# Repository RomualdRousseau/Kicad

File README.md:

# Kicad
Various Kicad Sketches to test new ideas

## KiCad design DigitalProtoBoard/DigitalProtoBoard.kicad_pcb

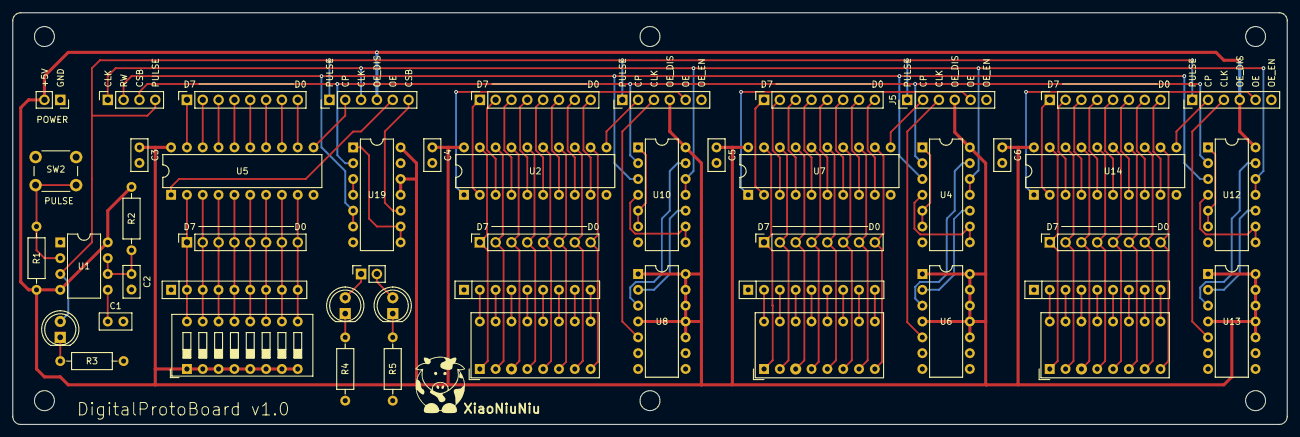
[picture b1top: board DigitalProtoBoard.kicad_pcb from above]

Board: 2 copper layers, 204.5 x 66.0 mm, 57 parts (0 on the bottom side), 128 nets.

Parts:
BAR1, BAR2, BAR3: SSB-LXH100SRW
C1, C2: 10nF; C_Disc_D5.0mm_W2.5mm_P2.50mm
C3, C4, C5, C6: 100nF; C_Disc_D5.0mm_W2.5mm_P2.50mm
D1, D2, D3: LED; LED_D5.0mm
H1, H3, H4, H4#2, H4#3, H4#4: MountingHole_3.2mm_M3
J1, J5, J8: R_CTRL; PinHeader_1x06_P2.54mm_Vertical
J2: POWER; PinSocket_1x02_P2.54mm_Vertical
J3: W_CTRL; PinHeader_1x06_P2.54mm_Vertical
J4, J6, J10: BIN; PinSocket_1x08_P2.54mm_Vertical
J7, J9, J11: RIN; PinSocket_1x08_P2.54mm_Vertical
J12: ROUT; PinSocket_1x08_P2.54mm_Vertical
J13: BOUT; PinSocket_1x08_P2.54mm_Vertical
J14: CONTROL; PinSocket_1x04_P2.54mm_Vertical
J15: LEDS; PinSocket_1x02_P2.54mm_Vertical
R1: 10K; R_Axial_DIN0207_L6.3mm_D2.5mm_P10.16mm_Horizontal
R2: 1M; R_Axial_DIN0207_L6.3mm_D2.5mm_P10.16mm_Horizontal
R3, R4, R5: 220; R_Axial_DIN0207_L6.3mm_D2.5mm_P10.16mm_Horizontal
RN1, RN2, RN3, RN4: 10K; R_Array_SIP9
SW1: INPUT; SW_DIP_SPSTx08_Slide_9.78x22.5mm_W7.62mm_P2.54mm
SW2: PULSE; SW_PUSH_6mm
U1: NE555P; DIP-8_W7.62mm
U2, U5, U7, U14: 74HC574; DIP-20_W7.62mm
U4, U10, U12, U19: 74HC02; DIP-14_W7.62mm
U6, U8, U13: 74HC74; DIP-14_W7.62mm
XiaoNiuNiu: LOGO; VerySmallCow

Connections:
+5V: C3.1, C4.1, C5.1, C6.1, J1.4, J2.2, J3.4, J5.4, J8.4, R1.1, R2.1, SW1.1, SW1.2, SW1.3, SW1.4, SW1.5, SW1.6, SW1.7, SW1.8, U1.4 (R), U1.8 (VCC), U2.20 (VCC), U4.14 (VCC), U5.20 (VCC), U6.1 (~R), U6.4 (~S), U6.10 (~S), U6.11 (C), U6.12 (D), U6.13 (~R), U6.14 (VCC), U7.20 (VCC), U8.1 (~R), U8.4 (~S), U8.10 (~S), U8.11 (C), U8.12 (D), U8.13 (~R), U8.14 (VCC), U10.14 (VCC), U12.14 (VCC), U13.1 (~R), U13.4 (~S), U13.10 (~S), U13.11 (C), U13.12 (D), U13.13 (~R), U13.14 (VCC), U14.20 (VCC), U19.11, U19.12, U19.14 (VCC)
/Read Register Addr1/CP: J5.2, U7.11 (Cp)
/Read Register Addr1/OE: J5.5, U7.1 (OE)
/Read Register Addr1/SYNC_CP: J5.3, U6.5 (Q)
/Read Register Addr2/CP: J8.2, U14.11 (Cp)
/Read Register Addr2/OE: J8.5, U14.1 (OE)
/Read Register Addr2/SYNC_CP: J8.3, U13.5 (Q)
/Read Register Data/CP: J1.2, U2.11 (Cp)
/Read Register Data/OE: J1.5, U2.1 (OE)
/Read Register Data/SYNC_CP: J1.3, U8.5 (Q)
/Write Register Data/CP: J3.2, U5.11 (Cp)
/Write Register Data/OE: J3.5, U5.1 (OE)
/Write Register Data/SYNC_OE: J3.6, U19.10
CLK: J3.3, J14.1, U4.11, U4.12, U10.11, U10.12, U12.11, U12.12
CSB: J14.3, U4.2, U10.2, U12.2, U19.2
GND: C1.2, C2.2, C3.2, C4.2, C5.2, C6.2, J1.6, J2.1, J5.6, J8.6, R3.2, R4.2, R5.2, RN1.1 (common), RN2.1 (common), RN3.1 (common), RN4.1 (common), SW2.1, U1.1 (GND), U2.10 (GND), U4.7 (GND), U5.10 (GND), U6.7 (GND), U7.10 (GND), U8.7 (GND), U10.7 (GND), U12.7 (GND), U13.7 (GND), U14.10 (GND), U19.7 (GND)
unnamed: D1.1 (K), R3.1
unnamed: D2.2 (A), J15.1
unnamed: D2.1 (K), R4.1
unnamed: D3.2 (A), J15.2
unnamed: D3.1 (K), R5.1
unnamed: J4.1, U2.2 (D0)
unnamed: J4.2, U2.3 (D1)
unnamed: J4.3, U2.4 (D2)
unnamed: J4.4, U2.5 (D3)
unnamed: J4.5, U2.6 (D4)
unnamed: J4.6, U2.7 (D5)
unnamed: J4.7, U2.8 (D6)
unnamed: J4.8, U2.9 (D7)
unnamed: J6.1, U7.2 (D0)
unnamed: J6.2, U7.3 (D1)
unnamed: J6.3, U7.4 (D2)
unnamed: J6.4, U7.5 (D3)
unnamed: J6.5, U7.6 (D4)
unnamed: J6.6, U7.7 (D5)
unnamed: J6.7, U7.8 (D6)
unnamed: J6.8, U7.9 (D7)
unnamed: BAR2.1 (A), J7.1, U7.19 (Q0)
unnamed: BAR2.2 (A), J7.2, U7.18 (Q1)
unnamed: BAR2.3 (A), J7.3, U7.17 (Q2)
unnamed: BAR2.4 (A), J7.4, U7.16 (Q3)
unnamed: BAR2.5 (A), J7.5, U7.15 (Q4)
unnamed: BAR2.6 (A), J7.6, U7.14 (Q5)
unnamed: BAR2.7 (A), J7.7, U7.13 (Q6)
unnamed: BAR2.8 (A), J7.8, U7.12 (Q7)
unnamed: BAR1.1 (A), J9.1, U2.19 (Q0)
unnamed: BAR1.2 (A), J9.2, U2.18 (Q1)
unnamed: BAR1.3 (A), J9.3, U2.17 (Q2)
unnamed: BAR1.4 (A), J9.4, U2.16 (Q3)
unnamed: BAR1.5 (A), J9.5, U2.15 (Q4)
unnamed: BAR1.6 (A), J9.6, U2.14 (Q5)
unnamed: BAR1.7 (A), J9.7, U2.13 (Q6)
unnamed: BAR1.8 (A), J9.8, U2.12 (Q7)
unnamed: J10.1, U14.2 (D0)
unnamed: J10.2, U14.3 (D1)
unnamed: J10.3, U14.4 (D2)
unnamed: J10.4, U14.5 (D3)
unnamed: J10.5, U14.6 (D4)
unnamed: J10.6, U14.7 (D5)
unnamed: J10.7, U14.8 (D6)
unnamed: J10.8, U14.9 (D7)
unnamed: BAR3.1 (A), J11.1, U14.19 (Q0)
unnamed: BAR3.2 (A), J11.2, U14.18 (Q1)
unnamed: BAR3.3 (A), J11.3, U14.17 (Q2)
unnamed: BAR3.4 (A), J11.4, U14.16 (Q3)
unnamed: BAR3.5 (A), J11.5, U14.15 (Q4)
unnamed: BAR3.6 (A), J11.6, U14.14 (Q5)
unnamed: BAR3.7 (A), J11.7, U14.13 (Q6)
unnamed: BAR3.8 (A), J11.8, U14.12 (Q7)
unnamed: J12.1, RN1.2 (R1), SW1.16, U5.2 (D0)
unnamed: J12.2, RN1.3 (R2), SW1.15, U5.3 (D1)
unnamed: J12.3, RN1.4 (R3), SW1.14, U5.4 (D2)
unnamed: J12.4, RN1.5 (R4), SW1.13, U5.5 (D3)
unnamed: J12.5, RN1.6 (R5), SW1.12, U5.6 (D4)
unnamed: J12.6, RN1.7 (R6), SW1.11, U5.7 (D5)
unnamed: J12.7, RN1.8 (R7), SW1.10, U5.8 (D6)
unnamed: J12.8, RN1.9 (R8), SW1.9, U5.9 (D7)
unnamed: J13.1, U5.19 (Q0)
unnamed: J13.2, U5.18 (Q1)
unnamed: J13.3, U5.17 (Q2)
unnamed: J13.4, U5.16 (Q3)
unnamed: J13.5, U5.15 (Q4)
unnamed: J13.6, U5.14 (Q5)
unnamed: J13.7, U5.13 (Q6)
unnamed: J13.8, U5.12 (Q7)
unnamed: BAR2.16 (K), RN2.2 (R1)
unnamed: BAR2.15 (K), RN2.3 (R2)
unnamed: BAR2.14 (K), RN2.4 (R3)
unnamed: BAR2.13 (K), RN2.5 (R4)
unnamed: BAR2.12 (K), RN2.6 (R5)
unnamed: BAR2.11 (K), RN2.7 (R6)
unnamed: BAR2.10 (K), RN2.8 (R7)
unnamed: BAR2.9 (K), RN2.9 (R8)
unnamed: BAR3.16 (K), RN3.2 (R1)
unnamed: BAR3.15 (K), RN3.3 (R2)
unnamed: BAR3.14 (K), RN3.4 (R3)
unnamed: BAR3.13 (K), RN3.5 (R4)
unnamed: BAR3.12 (K), RN3.6 (R5)
unnamed: BAR3.11 (K), RN3.7 (R6)
unnamed: BAR3.10 (K), RN3.8 (R7)
unnamed: BAR3.9 (K), RN3.9 (R8)
unnamed: BAR1.16 (K), RN4.2 (R1)
unnamed: BAR1.15 (K), RN4.3 (R2)
unnamed: BAR1.14 (K), RN4.4 (R3)
unnamed: BAR1.13 (K), RN4.5 (R4)
unnamed: BAR1.12 (K), RN4.6 (R5)
unnamed: BAR1.11 (K), RN4.7 (R6)
unnamed: BAR1.10 (K), RN4.8 (R7)
unnamed: BAR1.9 (K), RN4.9 (R8)
unnamed: C1.1, U1.5 (CV)
unnamed: C2.1, R2.2, U1.6 (THR), U1.7 (DIS)
unnamed: R1.2, SW2.2, U1.2 (TR)
unnamed: U4.1, U4.5, U4.6
unnamed: U4.4, U4.8, U4.9
unnamed: U4.13, U6.3 (C)
unnamed: U4.10, U6.2 (D)
unnamed: U8.3 (C), U10.13
unnamed: U8.2 (D), U10.10
unnamed: U10.1, U10.5, U10.6
unnamed: U10.4, U10.8, U10.9
unnamed: U12.1, U12.5, U12.6
unnamed: U12.4, U12.8, U12.9
unnamed: U12.13, U13.3 (C)
unnamed: U12.10, U13.2 (D)
unnamed: U19.1, U19.8, U19.9
unnamed: U19.3, U19.4
PULSE: D1.2 (A), J1.1, J3.1, J5.1, J8.1, J14.4, U1.3 (Q)
RW: J14.2, U4.3, U10.3, U12.3, U19.5, U19.6

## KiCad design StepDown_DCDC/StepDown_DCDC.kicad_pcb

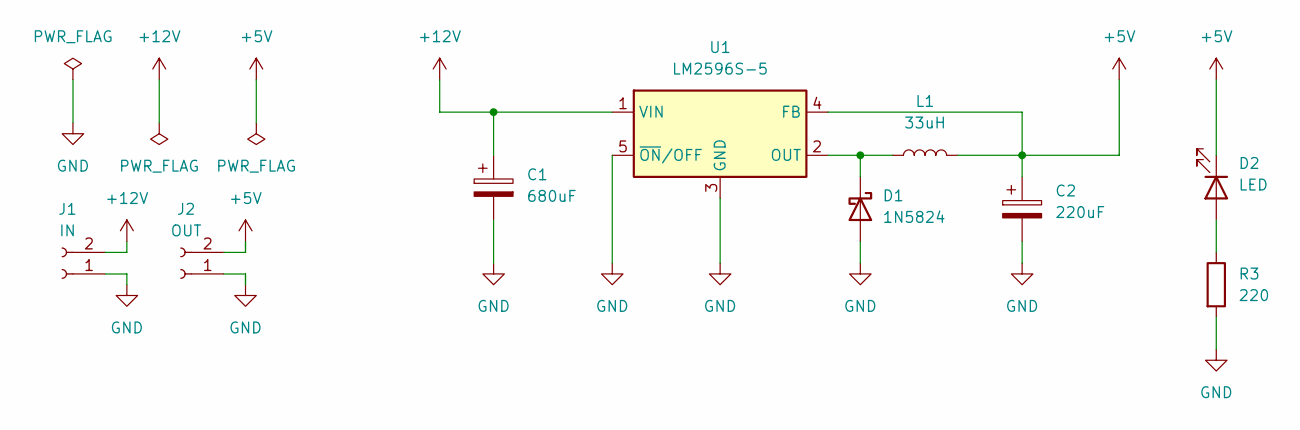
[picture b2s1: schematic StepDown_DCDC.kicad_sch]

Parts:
C1: 680uF; CP_Elec_10x10
C2: 220uF; CP_Elec_10x10
D1: 1N5824; D_SMA
D2: LED; LED_0805_2012Metric
J1: IN; Molex_KK-254_AE-6410-02A_1x02_P2.54mm_Vertical
J2: OUT; Molex_KK-254_AE-6410-02A_1x02_P2.54mm_Vertical
L1: 33uH; L_10.4x10.4_H4.8
R3: 220; R_0805_2012Metric
U1: LM2596S-5; TO-263-5_TabPin3

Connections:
+5V: C2.1, D2.1 (K), J2.2, L1.2, U1.4 (FB)
+12V: C1.1, J1.2, U1.1 (VIN)
GND: C1.2, C2.2, D1.2 (A), J1.1, J2.1, R3.2, U1.3 (GND), U1.5 (~ON/OFF)
unnamed: D1.1 (K), L1.1, U1.2 (OUT)
unnamed: D2.2 (A), R3.1

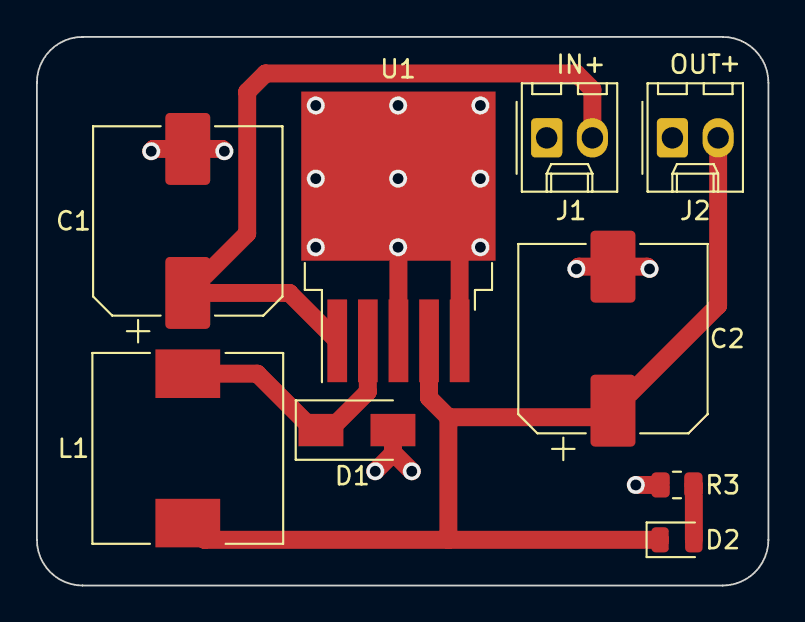
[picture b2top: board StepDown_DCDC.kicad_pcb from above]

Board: 2 copper layers, 40.6 x 30.5 mm, 9 parts (0 on the bottom side), 5 nets.

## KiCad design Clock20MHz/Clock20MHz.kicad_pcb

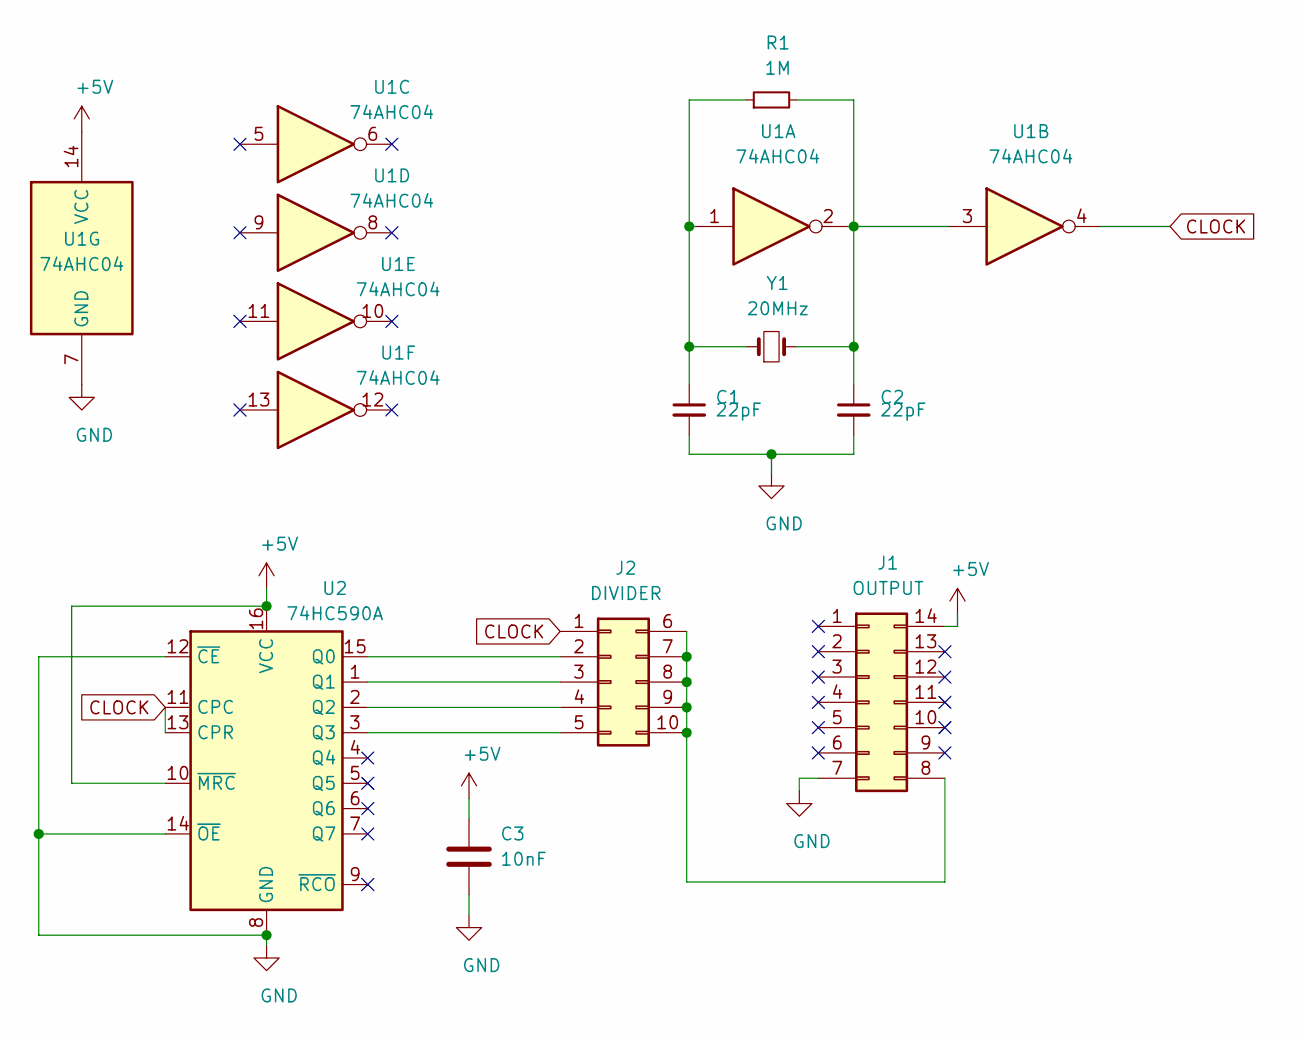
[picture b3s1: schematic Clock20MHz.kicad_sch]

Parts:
C1, C2: 22pF; C_Disc_D5.0mm_W2.5mm_P2.50mm
C3: 10nF; C_Disc_D5.0mm_W2.5mm_P2.50mm
J1: OUTPUT; DIP-14_W7.62mm
J2: DIVIDER; SW_DIP_SPSTx05_Slide_6.7x14.26mm_W7.62mm_P2.54mm_LowProfile
R1: 1M; R_Axial_DIN0207_L6.3mm_D2.5mm_P10.16mm_Horizontal
U1: 74AHC04; DIP-14_W7.62mm
U2: 74HC590A; DIP-16_W7.62mm
Y1: 20MHz; Crystal_HC18-U_Vertical

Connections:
+5V: C3.1, J1.14, U1.14 (VCC), U2.10 (~MRC), U2.16 (VCC)
CLOCK: J2.1, U1.4, U2.11 (CPC), U2.13 (CPR)
GND: C1.2, C2.2, C3.2, J1.7, U1.7 (GND), U2.8 (GND), U2.12 (~CE), U2.14 (~OE)
unnamed: C1.1, R1.1, U1.1, Y1.1
unnamed: C2.1, R1.2, U1.2, U1.3, Y1.2
unnamed: J1.8, J2.6, J2.7, J2.8, J2.9, J2.10
unnamed: J2.2, U2.15 (Q0)
unnamed: J2.3, U2.1 (Q1)
unnamed: J2.4, U2.2 (Q2)
unnamed: J2.5, U2.3 (Q3)

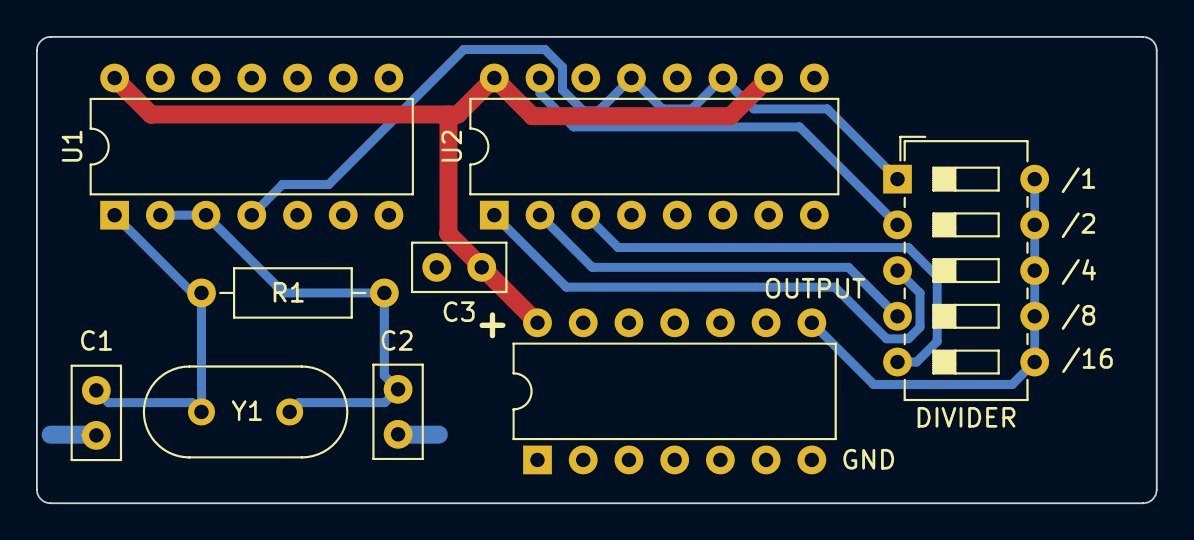
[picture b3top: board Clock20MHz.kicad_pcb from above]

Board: 2 copper layers, 62.2 x 25.9 mm, 9 parts (0 on the bottom side), 10 nets.

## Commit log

2021-12-20 Backup
2021-12-20 Move library to .local/share
2021-12-21 Ignore Kicad backups
2021-12-21 Cleanup
2022-02-05 First version
2023-05-06 Add libraries
2023-08-03 Restructure libraries
